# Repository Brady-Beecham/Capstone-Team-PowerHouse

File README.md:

# Parking Lot Monitoring System: Ground-Based Solution

## Executive Summary

This project is a continuation project from the 2022-23 academic year at Tennessee Technological University to monitor parking lots in a manner that allows students, faculty, staff, and campus visitors to find parking lots with availability in a timely manner. The previous team used cameras to monitor incoming and outgoing traffic in parking lots.  This solution will not work for many of the parking lots that do not have the infrastructure nearby to support cameras.  By using inductive loops to monitor designated entrances/exits of parking lots, more parking lots across campus can be monitored and students, faculty, etc. can find parking availability without having to search an entire parking lot in hopes of finding an open parking spot.

## Capabilities

Though this project is a continuation project, it deviates away from using cameras and instead uses a ground-based solution. 

The project is capable of...

1. Detecting vehicles entering/exiting parking lots that have designated entrances/exits.
2. Detecting vehicles traveling over the loops at 20 miles per hour or less with an accuracy of about 96%.
3. Using LoRaWAN to transmit data from an ESP32 at a designated entrance/exit of a parking lot to the LoRaWAN gateway. The gateway forwards packets to The Things Stack network server. The data is stored in an application on The Things Stack.
4. Utilizing solar power, wall outlet power, and battery power.

## Salient Outcomes

1. This project will continue the work of creating an effective Parking Lot Monitoring System.

   a. As of September 2023, the Parking Lot Monitoring System is in the second year of the overall project.  This team has inherited a previous system that used cameras to complete both static tracking (monitor parked cars) and dynamic tracking (cars entering and exiting lots) to efficiently monitor parking lots.  This method is a very efficient way to monitor parking lots; however, parking lots that are located away from campus buildings or do not have the infrastructure to support camera placement in the lots do not benefit from this method.  By using a ground-based solution to monitor parking lots with designated entrances/exits, more parking lots can be monitored across the campus of Tennessee Tech.

2. This project will implement the use of solar panels to efficiently power the system.

   a. Some parking lots across the campus of Tennessee Tech are not located near campus buildings.  To allow the system to work in these lots, solar panels will be used to power the system at these lots to efficiently monitor these lots so students, faculty, etc. know if there is parking availability at these specific lots.

3. This project will use LoRaWAN to transmit and receive data from the inductive loop sensor.

   a. LoRaWAN has been chosen for its superior range and lower power draw compared to WiFi.

## Project Demonstration & Images

### Project Video
https://www.youtube.com/watch?v=kGD3eaTffT4

### Project Images

*Charge Controller*

*Loop Controller*

*Power Controller for Solar Power*

*Wall Power Controller*

*ESP32 Microcontroller with RFM95W LoRa Transceiver*

*Raspberry Pi 4-based LoRaWAN Gateway with WM1302 Concentrator*

## About Us

### Team

Abdulrahman Alrudayan is a senior Electrical Engineering major at Tennessee Technological University.  His interests include power systems and digital design.  The main focus for Abdulrahman is designing the main power system that will distribute power to the entire system through the use of buck converters, step-down transformers, etc.

Khalifah Altamimi is a senior Electrical Engineering major at Tennessee Technological University.  His interests include power systems, robotics, and digital design.  The main focus for Khalifah is designing the backup power system that will provide power to allow the system to continue working when a power outage occurs on campus.  When the system is not being used, it will be charging and stay charged until backup power is needed for the system.

Brady Beecham is a senior Computer Engineering major with a minor in Mathematics at Tennessee Technological University.  His interests include embedded system firmware and design. He spent 7 months as an embedded systems software engineering intern at The Coats Company in Lavergne, TN. The main task Brady has is to power the system using solar power and backup batteries. This is going to be designed as an embedded system that will control the charging and discharging status of the batteries.

Kyle Plant is a senior Computer Engineering major with a minor in Computer Science at Tennessee Technological University.  His interests include programming, FPGA, VLSI, networks, embedded systems, artificial intelligence, automation, and more. He has had three internships during his time as an undergraduate. The first two were at Matheson, a producer of industrial, medical, and specialty gasses as well as gas handling equipment. His first internship at Matheson involved making user-friendly GUI dashboards to display graphs of gas purity or mixture ratio data as well as many other small projects. His second internship at Matheson involved performing general site IT duties as well as a few small projects. His third internship was with QMSI or Quality Manufacturing Systems, Inc. QMSI is an automation and systems integration company that specializes in automated pharmacy systems. At QMSI he worked with AutoCAD to make drawings for the conveyor lines and motor panels. The main focus for Kyle is designing a system to collect data from the loop detector, transmit data to a central computer, and store this data in a database within the central computer. This will involve microcontroller programming, wireless networking, and database management.

Michael Sisk is a senior Electrical Engineering major at Tennessee Technological University.  His interests include power systems, robotics, and automation.  He has spent eight months interning at Jack Daniels Distillery in Lynchburg, TN as an engineering maintenance intern.  He is also currently serving as the Engineering Joint Council (EJC) Representative for the student chapter of the Institute of Electrical and Electronics Engineers (IEEE).  The main focus for Michael Sisk is designing the ground-based sensor, which involves using a series of inductive loops to detect the presence of vehicles and determining whether a vehicle is entering or exiting a parking lot from the information given by the loops.

### Faculty Supervisor

Mr. Jesse Roberts - ECE Department

### Stakeholders

The primary customer for this project is the Naval Surface Warfare Center Dahlgren Division in Dahlgren, VA, which is under the command of the Naval Sea Systems Command (NAVSEA). 

One major stakeholder that will be affected by the project is commuter students.  Commuter students will use this system heavily as they must find parking in a timely manner in specific parking lots in order to be on time for class or extracurricular events on campus.

Another stakeholder that will be affected by the project is campus visitors.  For visitors that have come to Tennessee Tech University numerous times or for first-time visitors, it will be extremely useful in locating parking lots that have availability to allow them more time to complete business they have on campus and not have to spend a significant amount of time finding places to park on campus.

### Recognitions

Since this project is a continuation from the 2022-23 academic year, this team wants to recognize the previous Parking Lot Monitoring System team and their members: Kester Nucum, Aaron Wilhite, Gabriel Laboy, Genevieve Schreiber, and Reggie Garza.  This team consisted of three computer engineering students and two electrical engineering students.  With their knowledge and collaboration with the CSC team, they were successful in creating a server, sign, and cameras to detect and count the number of vehicles in a specified parking lot.  Due to their work, this team of three electrical engineering students and two computer engineering students were able to create a ground-based solution to assist the current camera system in detecting vehicles entering and leaving a parking lot and display an accurate number of available parking spots within a specific parking lot.

Another group to recognize for this project is the NAVSEA representatives from Dahlgren, VA: Robert Sexton and Kristen Voyles.  By having their knowledge and expertise of both electrical/computer engineering and the engineering design process, the team was able to learn how to successfully work together as a team while using the knowledge and skills each team member has obtained over the course of their undergraduate education and apply it to a real-world engineering problem.

For this project, the supervisor, Jesse Roberts, held an important role in this project.  Since this is a continuation project, the team relied heavily on Mr. Roberts' input as to what direction the project needed to go and also know the expected output of the project.  With Mr. Roberts' knowledge, the team was successful in finding faults in the previous team's work and was able to find a solution to aiding the use of cameras across parking lots.

## Repo Organization

For the layout of the team's Github, it includes three main folders: Documentation, Reports, and Software.  The three folders are explained in the following subsections.

### Reports

In the Reports folder, it contains documents such as the Project Proposal, Conceptual Design, Experimentation, Final Report, Lessons Learned, etc.  All documentation that is in the form of a report is located in this folder.  This folder also contains a broad explanation of the project from beginning to end in the numerous documents provided in this folder.

### Documentation

In the Documentation folder, folders such as 3D models, signoffs, team meeting minutes, etc. are found in this folder.  This contains very detailed explanations of the design process for the team.  The folder Meeting Minutes contains weekly updates from the team such as discussions between the team and decisions that the team made at these specific meetings.  The folder Electrical contains schematic drawings that were created and also PCB designs that the team used or considered using for the project.  To summarize, the Documentation folder contains very detailed explanations of the different steps in the design process and also the different discussions and decisions made by the team over the course of the project.

### Software

In the Software folder, an explanation of the different software files, code files, etc. is given.  Each software folder contains an explanation of what the software does, all dependencies of the software, how to install the software, and how to use the software.  For those that want to replicate the exact software used for this project, precise detail is given to ensure that the process of using the software is simple to repeat when recreating this project.

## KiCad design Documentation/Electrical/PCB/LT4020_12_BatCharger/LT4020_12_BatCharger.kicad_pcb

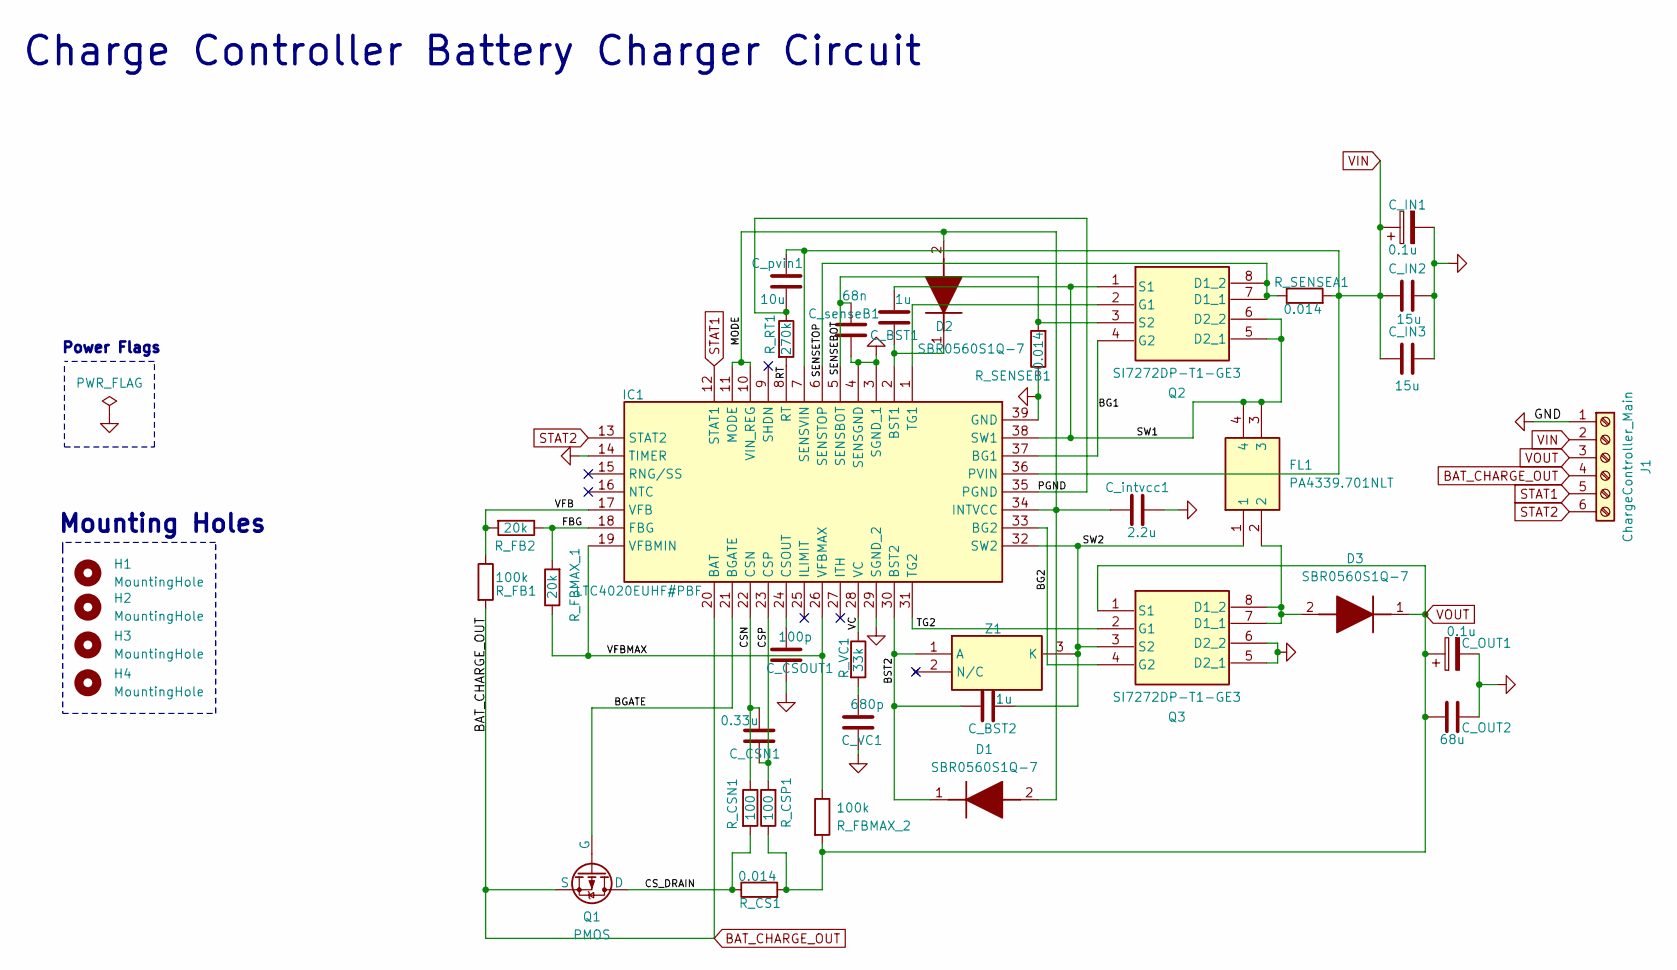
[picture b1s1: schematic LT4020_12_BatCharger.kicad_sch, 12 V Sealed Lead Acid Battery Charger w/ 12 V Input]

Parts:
C_BST1, C_BST2: 1u; C_1206_3216Metric_Pad1.33x1.80mm_HandSolder
C_CSN1: 0.33u; C_1206_3216Metric_Pad1.33x1.80mm_HandSolder
C_CSOUT1: 100p; C_1206_3216Metric_Pad1.33x1.80mm_HandSolder
C_IN1: 0.1u; C_1206_3216Metric_Pad1.33x1.80mm_HandSolder
C_IN2, C_IN3: 15u; C_1206_3216Metric_Pad1.33x1.80mm_HandSolder
C_OUT1: 0.1u; C_1206_3216Metric_Pad1.33x1.80mm_HandSolder
C_OUT2: 68u; C_1206_3216Metric_Pad1.33x1.80mm_HandSolder
C_VC1: 680p; C_1206_3216Metric_Pad1.33x1.80mm_HandSolder
C_intvcc1: 2.2u; C_1206_3216Metric_Pad1.33x1.80mm_HandSolder
C_pvin1: 10u; CAPPRD250W65D630H900
C_senseB1: 68n; C_1206_3216Metric_Pad1.33x1.80mm_HandSolder
D1, D2, D3: SBR0560S1Q-7; SOD3716X145N; Manufacturer_Part_Number SBR0560S1Q-7; Mouser Part Number 621-SBR0560S1Q-7
FL1: PA4339.701NLT; PA4339701NLT; Manufacturer_Part_Number PA4339.701NLT; Mouser Part Number 673-PA4339.701NLT
H1, H2, H3, H4: MountingHole; MountingHole_2.2mm_M2
IC1: LTC4020EUHF#PBF; QFN50P500X700X80-39N-D; Manufacturer_Part_Number LTC4020EUHF#PBF; Mouser Part Number N/A
J1: ChargeController_Main; SolderWire-1sqmm_1x06_P7.8mm_D1.4mm_OD3.9mm
Q1: PMOS; NVD5117PLT4GVF01
Q2, Q3: SI7272DP-T1-GE3; SI7288DPT1GE3; Manufacturer_Part_Number SI7272DP-T1-GE3; Mouser Part Number 781-SI7272DP-GE3
R_CS1: 0.014; R_1206_3216Metric_Pad1.30x1.75mm_HandSolder
R_CSN1: 100; R_1206_3216Metric_Pad1.30x1.75mm_HandSolder
R_CSP1: 100; R_1206_3216Metric_Pad1.30x1.75mm_HandSolder
R_FB1: 100k; R_Axial_DIN0309_L9.0mm_D3.2mm_P5.08mm_Vertical
R_FB2: 20k; R_1206_3216Metric_Pad1.30x1.75mm_HandSolder
R_FBMAX_1: 20k; R_1206_3216Metric_Pad1.30x1.75mm_HandSolder
R_FBMAX_2: 100k; R_Axial_DIN0309_L9.0mm_D3.2mm_P5.08mm_Vertical
R_RT1: 270k; R_1206_3216Metric_Pad1.30x1.75mm_HandSolder
R_SENSEA1: 0.014; R_1206_3216Metric_Pad1.30x1.75mm_HandSolder
R_SENSEB1: 0.014; R_1206_3216Metric_Pad1.30x1.75mm_HandSolder
R_VC1: 33k; R_Axial_DIN0309_L9.0mm_D3.2mm_P5.08mm_Vertical
Z1: BZX84C6V2LT116; SOT95P240X115-3N; Manufacturer_Part_Number BZX84C6V2LT116; Mouser Part Number 755-BZX84C6V2LT116

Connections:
/BG1: IC1.37 (BG1), Q2.4 (G2)
/BG2: IC1.33 (BG2), Q3.4 (G2)
/BGATE: IC1.21 (BGATE), Q1.2 (G)
/BST2: C_BST2.1, D1.1 (K), IC1.30 (BST2), Z1.1 (A)
/CSN: C_CSN1.1, IC1.22 (CSN), R_CSN1.1
/CSP: C_CSN1.2, IC1.23 (CSP), R_CSP1.2
/CS_DRAIN: Q1.1 (D), R_CS1.1, R_CSN1.2
/FBG: IC1.18 (FBG), R_FB2.1, R_FBMAX_1.2
/MODE: C_intvcc1.2, D1.2 (A), D2.2 (A), IC1.10 (VIN_REG), IC1.11 (MODE), IC1.34 (INTVCC)
/PGND: C_pvin1.2, IC1.35 (PGND), R_RT1.1
/RT: IC1.8 (RT), R_RT1.2
/SENSEBOT: C_senseB1.1, IC1.5 (SENSBOT), Q2.3 (S2), R_SENSEB1.2
/SENSETOP: IC1.6 (SENSTOP), Q2.7 (D1_1), Q2.8 (D1_2), Q2.9, Q2.11, R_SENSEA1.1
/SW1: C_BST1.1, FL1.3, FL1.4, IC1.38 (SW1), Q2.1 (S1), Q2.5 (D2_1), Q2.6 (D2_2), Q2.10, Q2.12
/SW2: C_BST2.2, FL1.1, IC1.32 (SW2), Q3.3 (S2), Z1.3 (K)
/TG2: IC1.31 (TG2), Q3.2 (G1)
/VC: IC1.28 (VC), R_VC1.1
/VFB: IC1.17 (VFB), R_FB1.1, R_FB2.2
/VFBMAX: IC1.19 (VFBMIN), IC1.26 (VFBMAX), R_FBMAX_1.1, R_FBMAX_2.1
BAT_CHARGE_OUT: IC1.20 (BAT), J1.4, Q1.3 (S), R_FB1.2
GND: C_CSOUT1.2, C_IN1.2, C_IN2.2, C_IN3.2, C_OUT1.2, C_OUT2.1, C_VC1.2, C_intvcc1.1, C_senseB1.2, IC1.3 (SGND_1), IC1.4 (SENSGND), IC1.14 (TIMER), IC1.29 (SGND_2), IC1.39 (GND), J1.1, Q3.5 (D2_1), Q3.6 (D2_2), Q3.12, R_SENSEB1.1
unnamed: C_VC1.1, R_VC1.2
unnamed: C_BST1.2, D2.1 (K), IC1.2 (BST1)
unnamed: D3.2 (A), FL1.2, Q3.7 (D1_1), Q3.8 (D1_2), Q3.9, Q3.11
unnamed: C_CSOUT1.1, IC1.24 (CSOUT)
unnamed: IC1.1 (TG1), Q2.2 (G1)
STAT1: IC1.12 (STAT1), J1.5
STAT2: IC1.13 (STAT2), J1.6
VIN: C_IN1.1, C_IN2.1, C_IN3.1, C_pvin1.1, IC1.7 (SENSVIN), IC1.36 (PVIN), J1.2, R_SENSEA1.2
VOUT: C_OUT1.1, C_OUT2.2, D3.1 (K), J1.3, Q3.1 (S1), R_CS1.2, R_CSP1.1, R_FBMAX_2.2

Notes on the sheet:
Power Flags
Charge Controller Battery Charger Circuit
Mounting Holes

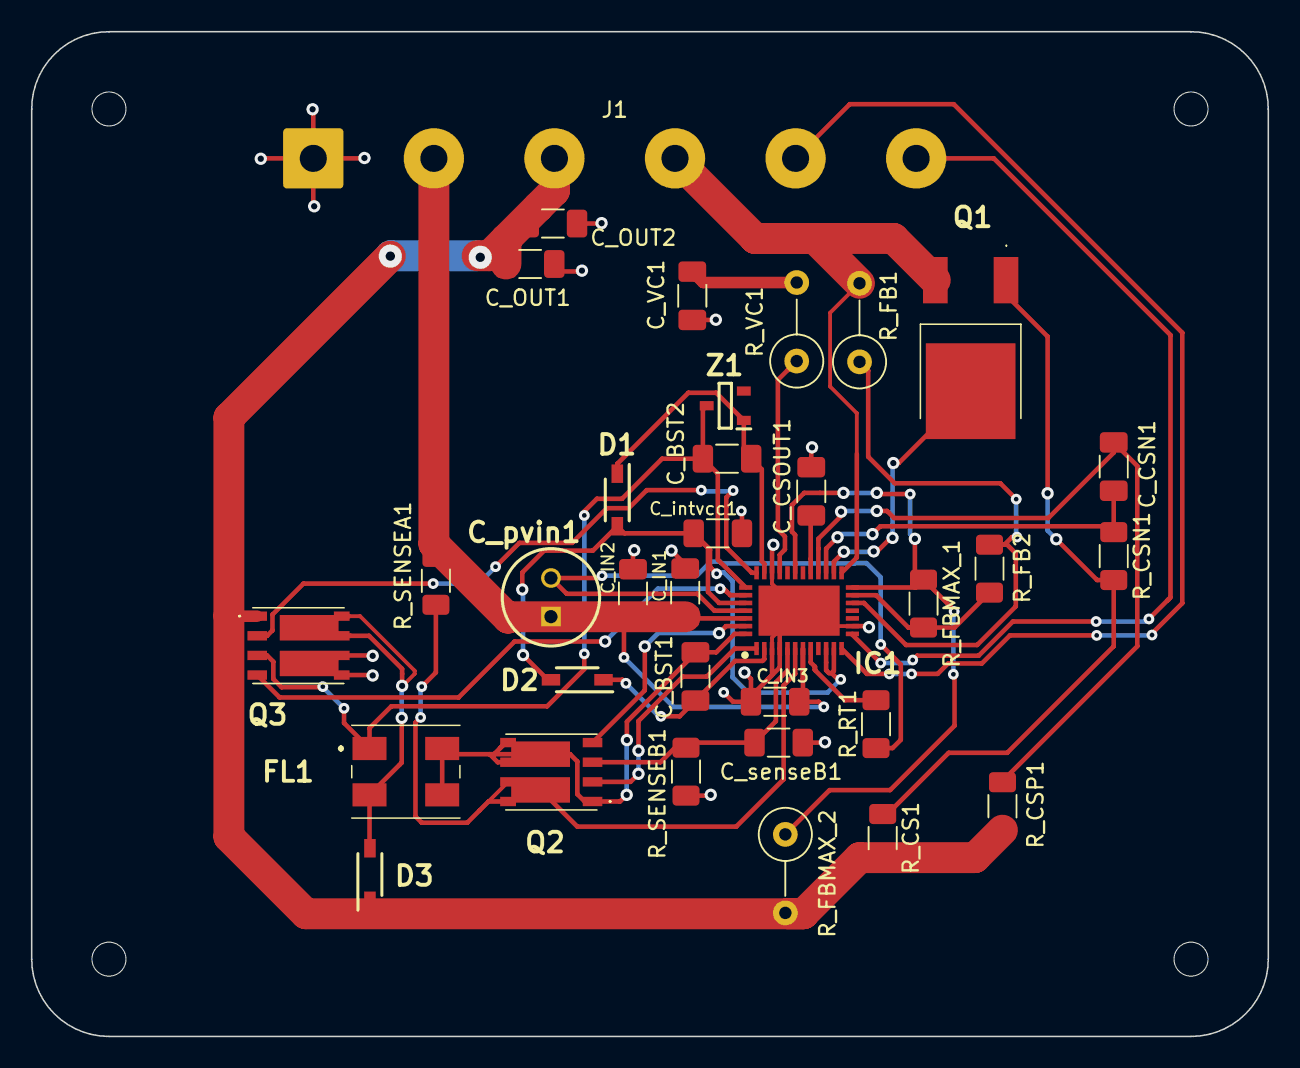
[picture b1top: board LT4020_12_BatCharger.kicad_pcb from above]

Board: 2 copper layers, 80.0 x 65.0 mm, 38 parts (0 on the bottom side), 30 nets.

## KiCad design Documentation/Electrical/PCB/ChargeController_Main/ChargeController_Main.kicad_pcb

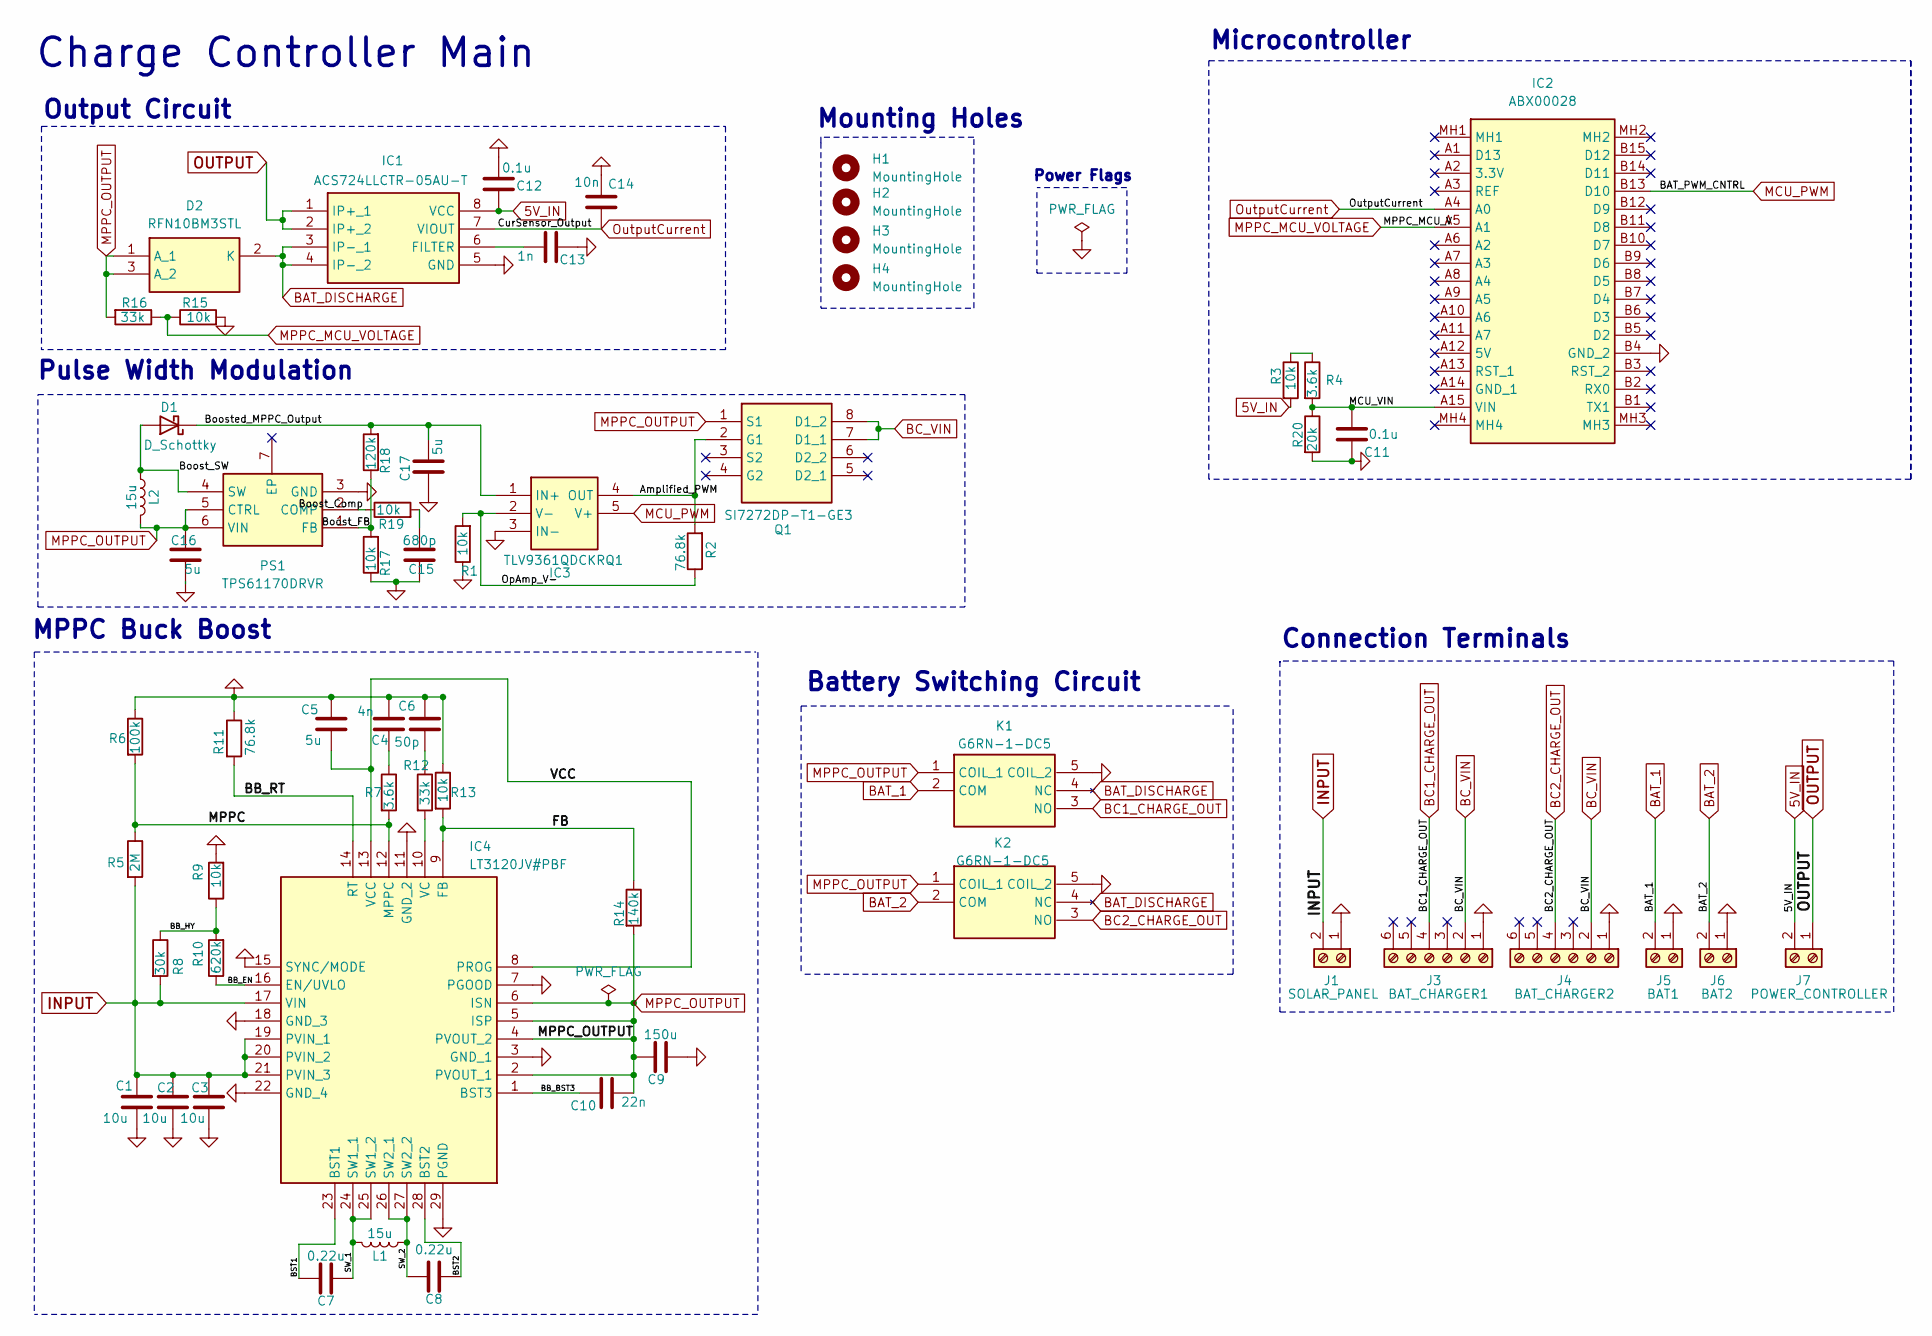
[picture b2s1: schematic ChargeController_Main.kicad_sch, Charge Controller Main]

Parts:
C1, C2, C3: 10u; CAPPRD250W65D630H900
C4: 4n; C_Disc_D14.5mm_W5.0mm_P7.50mm
C5, C16, C17: 5u; C_Radial_D6.3mm_H7.0mm_P2.50mm
C6: 50p; C_1206_3216Metric
C7, C8: 0.22u; C_Rect_L7.2mm_W2.5mm_P5.00mm_FKS2_FKP2_MKS2_MKP2
C9: 150u; CP_Radial_D6.3mm_P2.50mm
C10: 22n; C_1206_3216Metric_Pad1.33x1.80mm_HandSolder
C11, C12: 0.1u; C_1206_3216Metric_Pad1.33x1.80mm_HandSolder
C13: 1n; C_1206_3216Metric_Pad1.33x1.80mm_HandSolder
C14: 10n; C_1206_3216Metric_Pad1.33x1.80mm_HandSolder
C15: 680p; C_1206_3216Metric_Pad1.33x1.80mm_HandSolder
D1: D_Schottky; SOD3716X145N
D2: RFN10BM3STL; RD3P175SNFRATL; Mouser Part Number 755-RFN10BM3STL
H1, H2, H3, H4: MountingHole; MountingHole_2.2mm_M2
IC1: ACS724LLCTR-05AU-T; SOIC127P600X175-8N; Manufacturer_Part_Number ACS724LLCTR-05AU-T; Mouser Part Number 250-724LLCTR05AUT
IC2: ABX00028
IC3: TLV9361QDCKRQ1; SOT65P210X110-5N; Manufacturer_Part_Number TLV9361QDCKRQ1; Mouser Part Number 595-TLV9361QDCKRQ1
IC4: LT3120JV#PBF; QFN50P400X500X83-29N-D; Manufacturer_Part_Number LT3120JV#PBF; Mouser Part Number 584-LT3120JV#PBF
J1: SOLAR_PANEL; SolderWire-1sqmm_1x02_P5.4mm_D1.4mm_OD2.7mm
J3: BAT_CHARGER1; SolderWire-1sqmm_1x06_P5.4mm_D1.4mm_OD2.7mm
J4: BAT_CHARGER2; SolderWire-1sqmm_1x06_P5.4mm_D1.4mm_OD2.7mm
J5: BAT1; SolderWire-1sqmm_1x02_P5.4mm_D1.4mm_OD2.7mm
J6: BAT2; SolderWire-1sqmm_1x02_P5.4mm_D1.4mm_OD2.7mm
J7: POWER_CONTROLLER; SolderWire-1sqmm_1x02_P5.4mm_D1.4mm_OD2.7mm
K1, K2: G6RN-1-DC5; G6RN1DC5; Manufacturer_Part_Number G6RN-1-DC5; Mouser Part Number 653-G6RN-1-DC5
L1, L2: 15u; INDPM135125X500N
PS1: TPS61170DRVR; SON65P200X200X80-7N; Manufacturer_Part_Number TPS61170DRVR; Mouser Part Number 595-TPS61170DRVR
Q1: SI7272DP-T1-GE3; SI7288DPT1GE3; Manufacturer_Part_Number SI7272DP-T1-GE3; Mouser Part Number 781-SI7272DP-GE3
R1, R3, R9, R13, R15, R17, R19: 10k; R_Axial_DIN0309_L9.0mm_D3.2mm_P5.08mm_Vertical
R2, R11: 76.8k; R_Axial_DIN0309_L9.0mm_D3.2mm_P5.08mm_Vertical
R4, R7: 3.6k; R_Axial_DIN0309_L9.0mm_D3.2mm_P5.08mm_Vertical
R5: 2M; R_1206_3216Metric_Pad1.30x1.75mm_HandSolder
R6: 100k; R_Axial_DIN0309_L9.0mm_D3.2mm_P5.08mm_Vertical
R8: 30k; R_2512_6332Metric_Pad1.40x3.35mm_HandSolder
R10: 620k; R_2512_6332Metric_Pad1.40x3.35mm_HandSolder
R12, R16: 33k; R_Axial_DIN0309_L9.0mm_D3.2mm_P5.08mm_Vertical
R14: 140k; R_2512_6332Metric_Pad1.40x3.35mm_HandSolder
R18: 120k; R_1206_3216Metric_Pad1.30x1.75mm_HandSolder
R20: 20k; R_1206_3216Metric_Pad1.30x1.75mm_HandSolder

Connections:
5V_IN: C12.2, IC1.8 (VCC), J7.2, R3.2
/Amplified_PWM: IC3.4 (OUT), Q1.2 (G1), R2.2
/BB_BST3: C10.2, IC4.1 (BST3)
/BB_EN: IC4.16 (EN/UVLO), R10.1
/BB_HY: R8.1, R9.1, R10.2
/BB_RT: IC4.14 (RT), R11.2
/BST1: C7.1, IC4.23 (BST1)
/BST2: C8.2, IC4.28 (BST2)
/Boost_Comp: PS1.2 (COMP), R19.1
/Boost_FB: PS1.1 (FB), R17.2, R18.1
/Boost_SW: D1.2 (A), L2.1, PS1.4 (SW)
/Boosted_MPPC_Output: C17.1, D1.1 (K), IC3.1 (IN+), R18.2
/FB: IC4.9 (FB), R13.2, R14.1
/MCU_VIN: C11.1, IC2.A15 (VIN), R4.2, R20.1
/MPPC: IC4.12 (MPPC), R5.1, R6.2, R7.2
/OpAmp_V-: IC3.2 (V-), R1.2, R2.1
/SW_1: C7.2, IC4.24 (SW1_1), IC4.25 (SW1_2), L1.2
/SW_2: C8.1, IC4.26 (SW2_1), IC4.27 (SW2_2), L1.1
/VCC: C5.2, IC4.8 (PROG), IC4.13 (VCC)
BAT_1: J5.2, K1.2 (COM)
BAT_2: J6.2, K2.2 (COM)
BAT_DISCHARGE: D2.2 (K), IC1.3 (IP-_1), IC1.4 (IP-_2), K1.4 (NC), K2.4 (NC)
BC1_CHARGE_OUT: J3.4, K1.3 (NO)
BC2_CHARGE_OUT: J4.4, K2.3 (NO)
BC_VIN: J3.2, J4.2, Q1.7 (D1_1), Q1.8 (D1_2), Q1.9, Q1.11
GND: C1.2, C2.2, C3.2, C4.1, C5.1, C6.1, C9.2, C11.2, C12.1, C13.2, C14.2, C15.2, C16.1, C17.2, IC1.5 (GND), IC2.B4 (GND_2), IC3.3 (IN-), IC4.3 (GND_1), IC4.7 (PGOOD), IC4.11 (GND_2), IC4.15 (SYNC/MODE), IC4.18 (GND_3), IC4.22 (GND_4), IC4.29 (PGND), J1.1, J3.1, J4.1, J5.1, J6.1, K1.5 (COIL_2), K2.5 (COIL_2), PS1.3 (GND), PS1.7 (EP), R1.1, R6.1, R9.2, R11.1, R13.1, R15.2, R17.1, R20.2
INPUT: C1.1, C2.1, C3.1, IC4.17 (VIN), IC4.19 (PVIN_1), IC4.20 (PVIN_2), IC4.21 (PVIN_3), J1.2, R5.2, R8.2
MCU_PWM: IC2.B13 (D10), IC3.5 (V+)
MPPC_MCU_VOLTAGE: IC2.A5 (A1), R15.1, R16.1
MPPC_OUTPUT: C9.1, C10.1, C16.2, D2.1 (A_1), D2.3 (A_2), IC4.2 (PVOUT_1), IC4.4 (PVOUT_2), IC4.5 (ISP), IC4.6 (ISN), K1.1 (COIL_1), K2.1 (COIL_1), L2.2, PS1.5 (CTRL), PS1.6 (VIN), Q1.1 (S1), R14.2, R16.2
unnamed: C4.2, R7.1
unnamed: C6.2, R12.1
unnamed: C15.1, R19.2
unnamed: C13.1, IC1.6 (FILTER)
unnamed: IC4.10 (VC), R12.2
unnamed: R3.1, R4.1
OUTPUT: IC1.1 (IP+_1), IC1.2 (IP+_2), J7.1
OutputCurrent: C14.1, IC1.7 (VIOUT), IC2.A4 (A0)

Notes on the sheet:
Output Circuit
MPPC Buck Boost
Charge Controller Main
Power Flags
Microcontroller
Mounting Holes
Battery Switching Circuit
Connection Terminals
Pulse Width Modulation

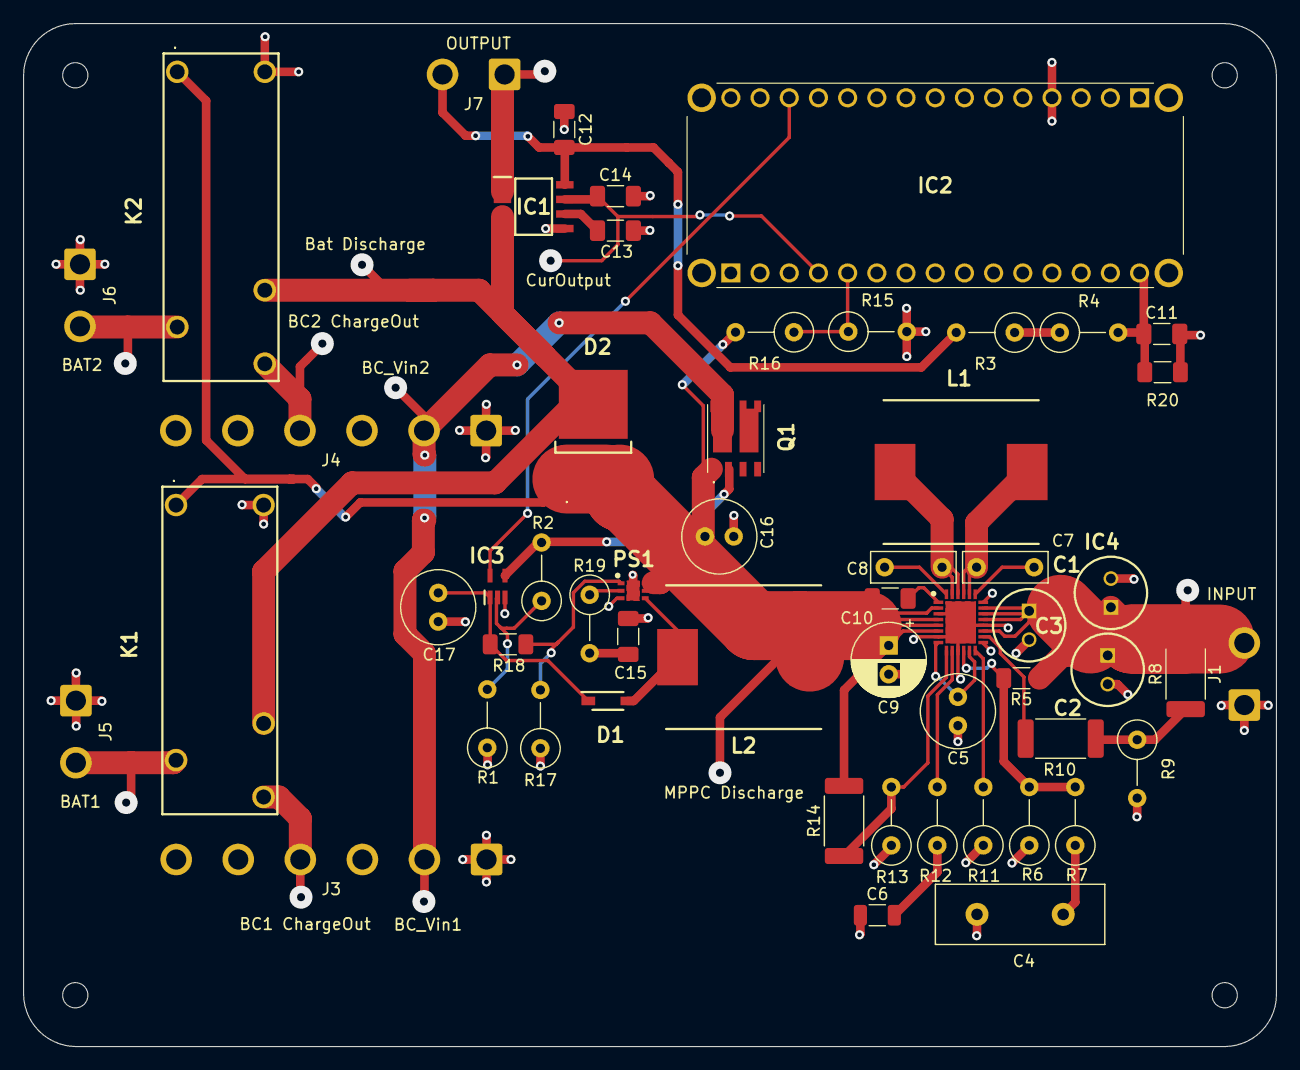
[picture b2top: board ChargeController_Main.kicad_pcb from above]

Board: 2 copper layers, 109.0 x 89.0 mm, 59 parts (0 on the bottom side), 38 nets.

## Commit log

2023-09-13 Add files via upload
    Project proposal first draft
2024-02-17 Update References, Analysis, Buildable Schematic
2024-02-20 Initial Charge Controller Main Loop Commit
    Added .h and .ino (to be .c) files and placed some skeleton code inside.
2024-02-27 Updating skeleton code
    Working towards minimal functionality
2024-04-05 Rename Experimentation.md to Experimentation Template.md
2024-04-05 Create Experimentation.md
    Completion of Loop Controller
2024-04-08 Added all constraints to file
2024-04-08 Corrected formatting
2024-04-08 Corrected Wrong constraint origins
2024-04-08 Update Experimentation.md
    Update of Constraints Section in Loop Controller Section
2024-04-09 Create test
2024-04-09 Added experiment sections for all subsystems
2024-04-09 Added Measures of Success Table
2024-04-09 Added Minimal Charge Controller Experimentation
2024-04-10 Update Experimentation.md
    Update of C10, C15-16, and C19 in Loop Controller
2024-04-10 Added requirements of deliverable to charge controller section to be completed at a later time
2024-04-10 Charge Controller Continued analysis with C28
2024-04-11 Update Experimentation.md
    Update of C11, C14 in Loop Controller
2024-04-11 Added Charge Controller Main PCB Problems analysis
2024-04-11 Corrected Data constraints table
2024-04-12 Updates to loop, ground based sensor, power controller sections
2024-04-12 Updates to charge controller section
2024-04-12 Update Experimental Procedure of Loop Controller
2024-04-12 Updated Charge Controller Experimentation
2024-04-15 Updates to Data System section
2024-04-15 Charge Controller Battery Charging PCB Problems
2024-04-15 Update Loop Controller Constraints, Minor Adjustments
2024-04-15 Charge Controller Removal of Proposed Changes Section
2024-04-15 Rename Minutes - 04-12-2024.md to Minutes - 2024-04-12.md
2024-04-15 Update Experimentation in Loop Controller
2024-04-16 Addressed relevant measures of success in data subsystem section
2024-04-16 Update Power Controller
2024-04-16 Update power Controller results
2024-04-17 Update Power controller updates
2024-04-17 Update Power Controller graphs update
2024-04-17 Update Power Controller graph update
2024-04-17 Update power controller final update
2024-04-17 Added ESP32 testing to Loop Controller section
2024-04-17 Update Experimentation, Design Changes of Loop Controller
2024-04-17 Wall Power Clean Up
2024-04-17 Fixed Typos in Wall Power
2024-04-17 Update Experimentation, Design Changes in Loop Controller
2024-04-17 Power Controller Clean Up
2024-04-17 Solar Clean Up
2024-04-17 Update Experimentation, Design Changes for Loop Controller
2024-04-17 Update Experimentation, Design Changes
2024-04-17 Update Experimentation, System Constraints Spelling
2024-04-17 Update Experimentation, Design Changes and Constraints Update of Loop Controller
2024-04-17 Made freq vs time graphs for ESP32 testing smaller
2024-04-18 Update Michael Sisk's Section
2024-04-23 Create Courses used during Capstone.md, Update Michael Sisk's Section
2024-04-24 Update Project Demo and Images for ReadMe on Main Page
2024-04-27 Update Kyle Plant's Section
2024-04-28 Set format for lessons learned
2024-04-28 Brady Lessons Learned
2024-04-28 Brady - grammar for my section
2024-04-28 Brady Beecham Individual Technical Presentation
2024-04-28 Uploaded Kyle Plant's Technical presentation
2024-04-28 Added link to video of Kyle Plant's technical presentation in readme
2024-04-28 Changed wording in readme
2024-04-28 Added ESP32 image to README.md
2024-04-28 Alrudayan-wall-power-individual-presentation
2024-04-29 Brady courses used
2024-04-29 Added Picture of LoRaWAN gateway to README.md
2024-04-29 Charge Controller Main PCB
2024-04-29 Battery Charging PCB Upload
2024-04-29 Updated Capabilities section of README.md
2024-04-29 Removed brackets around title of README.md
2024-04-29 Updated Data Subsystem section of Experimentation.md
